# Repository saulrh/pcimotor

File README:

I2C Interface:

--------------------------------------------------
software stop
  0x00

--------------------------------------------------
pause
  0x01

--------------------------------------------------
set controller sensor channel
  0x02

--------------------------------------------------
set controller motor channel
  0x03

--------------------------------------------------
set controller P
  0x04

--------------------------------------------------
set controller I
  0x05

--------------------------------------------------
set controller D
  0x06

--------------------------------------------------
set controller target
  0x07

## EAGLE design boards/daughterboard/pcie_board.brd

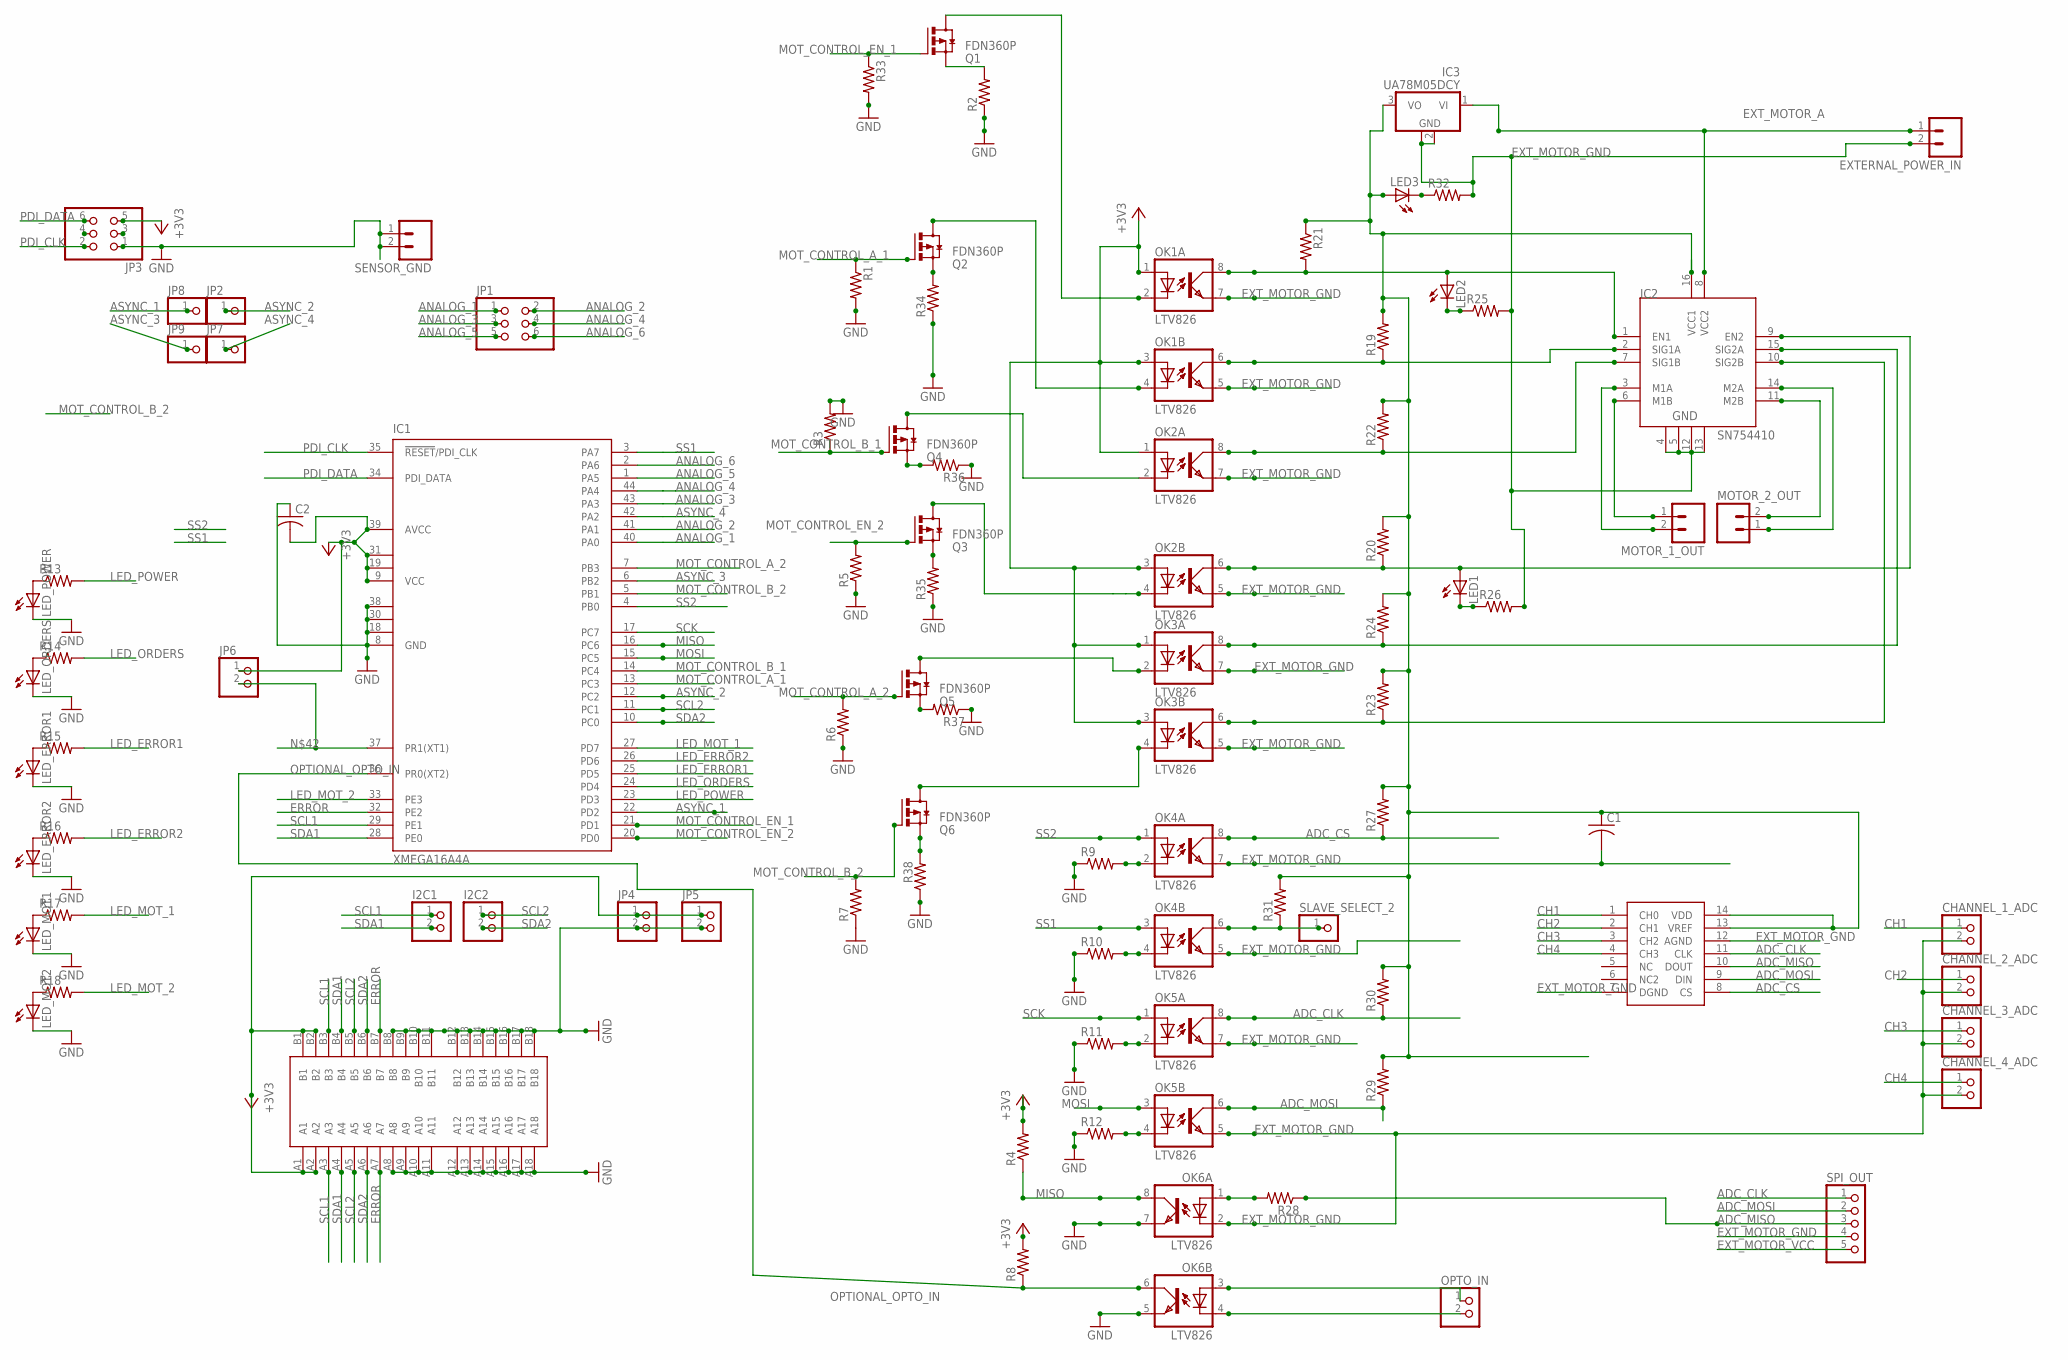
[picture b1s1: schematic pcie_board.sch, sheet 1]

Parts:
C1, C2: C-US025-040X050; C025-040X050
CHANNEL_1_ADC, CHANNEL_2_ADC, CHANNEL_3_ADC, CHANNEL_4_ADC: PINHD-1X2; 1X02
EXTERNAL_POWER_IN: M023.5MM; SCREWTERMINAL-3.5MM-2
I2C1, I2C2: PINHD-1X2; 1X02
IC1: XMEGA16A4A; TQFP44
IC2: SN754410; DIP16
IC3: UA78M05DCY; SOT223
JP1, JP3: PINHD-2X3; 2X03
JP2, JP7, JP8, JP9: PINHD-1X1; 1X01
JP4, JP5, JP6: PINHD-1X2; 1X02
LED1, LED2, LED3: LEDCHIP-LED0603; CHIP-LED0603
LED_ERROR1, LED_ERROR2: LED5MM
LED_MOT1, LED_MOT2: LED5MM
LED_ORDERS: LED5MM
LED_POWER: LED5MM
MOTOR_1_OUT, MOTOR_2_OUT: M023.5MM; SCREWTERMINAL-3.5MM-2
OK1, OK2, OK3, OK4, OK5, OK6: LTV826; DIL08
OPTO_IN: PINHD-1X2; 1X02
Q1, Q2, Q3, Q4, Q5, Q6: FDN360P; SUPER-SOT3
R1, R2, R3, R4, R5, R6, R7, R8, R9, R10, R11, R12, R13, R14, R15, R16, R17, R18, R19, R20, R21, R22, R23, R24, R25, R26, R27, R28, R29, R30, R31, R32, R33, R34, R35, R36, R37, R38: R-US_M0805; M0805
SENSOR_GND: M023.5MM; SCREWTERMINAL-3.5MM-2
SLAVE_SELECT_2: PINHD-1X1; 1X01
SPI_OUT: PINHD-1X5; 1X05
U$1: PCI-E1X_EDGE; PCI-E_X1_EDGE
U$2: MCP3004; DIL14

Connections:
+3V3: C2.2, IC1.9 (VCC), IC1.19 (VCC1), IC1.31 (VCC2), IC1.39 (AVCC), JP3.5, JP4.1, JP5.1, JP6.1, OK1.1 (A), OK1.3 (A), OK2.1 (A), OK2.3 (A), OK3.1 (A), OK3.3 (A), R4.2, R8.2, U$1.A1, U$1.A2, U$1.B1, U$1.B2
ADC_CLK: OK5.8 (COL), R30.1, SPI_OUT.1, U$2.11 (CLK)
ADC_CS: OK4.8 (COL), R27.1, U$2.8 (CS)
ADC_MISO: R28.1, SPI_OUT.3, U$2.10 (DOUT)
ADC_MOSI: OK5.6 (COL), R29.1, SPI_OUT.2, U$2.9 (DIN)
ANALOG_1: IC1.40 (PA0), JP1.1
ANALOG_2: IC1.41 (PA1), JP1.2
ANALOG_3: IC1.43 (PA3), JP1.3
ANALOG_4: IC1.44 (PA4), JP1.4
ANALOG_5: IC1.1 (PA5), JP1.5
ANALOG_6: IC1.2 (PA6), JP1.6
ASYNC_1: IC1.22 (PD2), JP8.1
ASYNC_2: IC1.12 (PC2), JP2.1
ASYNC_3: IC1.6 (PB2), JP9.1
ASYNC_4: IC1.42 (PA2), JP7.1
CH1: CHANNEL_1_ADC.1, U$2.1 (CH0)
CH2: CHANNEL_2_ADC.1, U$2.2 (CH1)
CH3: CHANNEL_3_ADC.1, U$2.3 (CH2)
CH4: CHANNEL_4_ADC.1, U$2.4 (CH3)
ERROR: IC1.32 (PE2), U$1.A7, U$1.B7
EXT_MOTOR_A: EXTERNAL_POWER_IN.1, IC2.8 (VCC2), IC3.1 (VI)
EXT_MOTOR_GND: C1.2, CHANNEL_1_ADC.2, CHANNEL_2_ADC.2, CHANNEL_3_ADC.2, CHANNEL_4_ADC.2, EXTERNAL_POWER_IN.2, IC2.4, IC2.5, IC2.12, IC2.13, IC3.2 (GND), IC3.4 (GND), OK1.5 (EMIT), OK1.7 (EMIT), OK2.5 (EMIT), OK2.7 (EMIT), OK3.5 (EMIT), OK3.7 (EMIT), OK4.5 (EMIT), OK4.7 (EMIT), OK5.5 (EMIT), OK5.7 (EMIT), OK6.2 (C), R25.2, R26.2, R32.2, SPI_OUT.4, U$2.7 (DGND), U$2.12 (AGND)
EXT_MOTOR_VCC: C1.1, IC2.16 (VCC1), IC3.3 (VO), LED3.A, R19.2, R20.2, R21.1, R22.2, R23.2, R24.2, R27.2, R29.2, R30.2, R31.2, SPI_OUT.5, U$2.13 (VREF), U$2.14 (VDD)
GND: C2.1, IC1.8 (GND), IC1.18 (GND1), IC1.30 (GND2), IC1.38 (GND3), JP3.1, JP4.2, JP5.2, LED_ERROR1.K (C), LED_ERROR2.K (C), LED_MOT1.K (C), LED_MOT2.K (C), LED_ORDERS.K (C), LED_POWER.K (C), OK6.5 (EMIT), OK6.7 (EMIT), R1.2, R2.1, R3.2, R5.1, R6.1, R7.1, R9.1, R10.1, R11.1, R12.1, R33.2, R34.1, R35.1, R36.1, R37.1, R38.1, SENSOR_GND.1, SENSOR_GND.2, U$1.A8, U$1.A9, U$1.A10, U$1.A11, U$1.A12, U$1.A13, U$1.A14, U$1.A15, U$1.A16, U$1.A17, U$1.A18, U$1.B8, U$1.B9, U$1.B10, U$1.B11, U$1.B12, U$1.B13, U$1.B14, U$1.B15, U$1.B16, U$1.B17, U$1.B18
LED_ERROR1: IC1.25 (PD5), R15.2
LED_ERROR2: IC1.26 (PD6), R16.2
LED_MOT_1: IC1.27 (PD7), R17.2
LED_MOT_2: IC1.33 (PE3), R18.2
LED_ORDERS: IC1.24 (PD4), R14.2
LED_POWER: IC1.23 (PD3), R13.2
MISO: IC1.16 (PC6), OK6.8 (COL), R4.1
MOSI: IC1.15 (PC5), OK5.3 (A)
MOT_CONTROL_A_1: IC1.13 (PC3), Q2.1 (G), R1.1
MOT_CONTROL_A_2: IC1.7 (PB3), Q5.1 (G), R6.2
MOT_CONTROL_B_1: IC1.14 (PC4), Q4.1 (G), R3.1
MOT_CONTROL_B_2: IC1.5 (PB1), Q6.1 (G), R7.2
MOT_CONTROL_EN_1: IC1.21 (PD1), Q1.1 (G), R33.1
MOT_CONTROL_EN_2: IC1.20 (PD0), Q3.1 (G), R5.2
unnamed: IC2.14 (M2A), MOTOR_2_OUT.1
unnamed: Q1.2 (S), R2.2
unnamed: IC2.11 (M2B), MOTOR_2_OUT.2
unnamed: OK1.2 (C), Q1.3 (D)
unnamed: Q2.2 (S), R34.2
unnamed: OK1.4 (C), Q2.3 (D)
unnamed: Q4.2 (S), R36.2
unnamed: OK4.2 (C), R9.2
unnamed: OK2.4 (C), Q3.3 (D)
unnamed: OK3.2 (C), Q5.3 (D)
unnamed: Q5.2 (S), R37.2
unnamed: OK4.4 (C), R10.2
unnamed: OK5.2 (C), R11.2
unnamed: OK5.4 (C), R12.2
unnamed: Q3.2 (S), R35.2
unnamed: LED_POWER.A, R13.1
unnamed: LED_ORDERS.A, R14.1
unnamed: OK2.2 (C), Q4.3 (D)
unnamed: OK4.6 (COL), R31.1, SLAVE_SELECT_2.1
unnamed: LED_ERROR1.A, R15.1
unnamed: LED_ERROR2.A, R16.1
unnamed: LED_MOT1.A, R17.1
unnamed: LED_MOT2.A, R18.1
unnamed: IC2.1 (EN1), LED2.A, OK1.8 (COL), R21.2
unnamed: IC2.2 (SIG1A), OK1.6 (COL), R19.1
unnamed: LED2.C, R25.1
unnamed: LED1.C, R26.1
unnamed: IC2.9 (EN2), LED1.A, OK2.6 (COL), R20.1
unnamed: IC2.7 (SIG1B), OK2.8 (COL), R22.1
unnamed: IC2.15 (SIG2A), OK3.8 (COL), R24.1
unnamed: IC2.3 (M1A), MOTOR_1_OUT.2
unnamed: IC2.6 (M1B), MOTOR_1_OUT.1
unnamed: IC2.10 (SIG2B), OK3.6 (COL), R23.1
unnamed: OK6.1 (A), R28.2
unnamed: OK6.3 (A), OPTO_IN.1
unnamed: OK6.4 (C), OPTO_IN.2
unnamed: LED3.C, R32.1
unnamed: Q6.2 (S), R38.2
unnamed: OK3.4 (C), Q6.3 (D)
unnamed: IC1.37 (PR1(XT1)), JP6.2
OPTIONAL_OPTO_IN: IC1.36 (PR0(XT2)), OK6.6 (COL), R8.1
PDI_CLK: IC1.35 (!RESET!/PDI_CLK), JP3.2
PDI_DATA: IC1.34 (PDI_DATA), JP3.6
SCK: IC1.17 (PC7), OK5.1 (A)
SCL1: I2C1.1, IC1.29 (PE1), U$1.A3, U$1.B3
SCL2: I2C2.1, IC1.11 (PC1), U$1.A5, U$1.B5
SDA1: I2C1.2, IC1.28 (PE0), U$1.A4, U$1.B4
SDA2: I2C2.2, IC1.10 (PC0), U$1.A6, U$1.B6
SS1: IC1.3 (PA7), OK4.3 (A)
SS2: IC1.4 (PB0), OK4.1 (A)

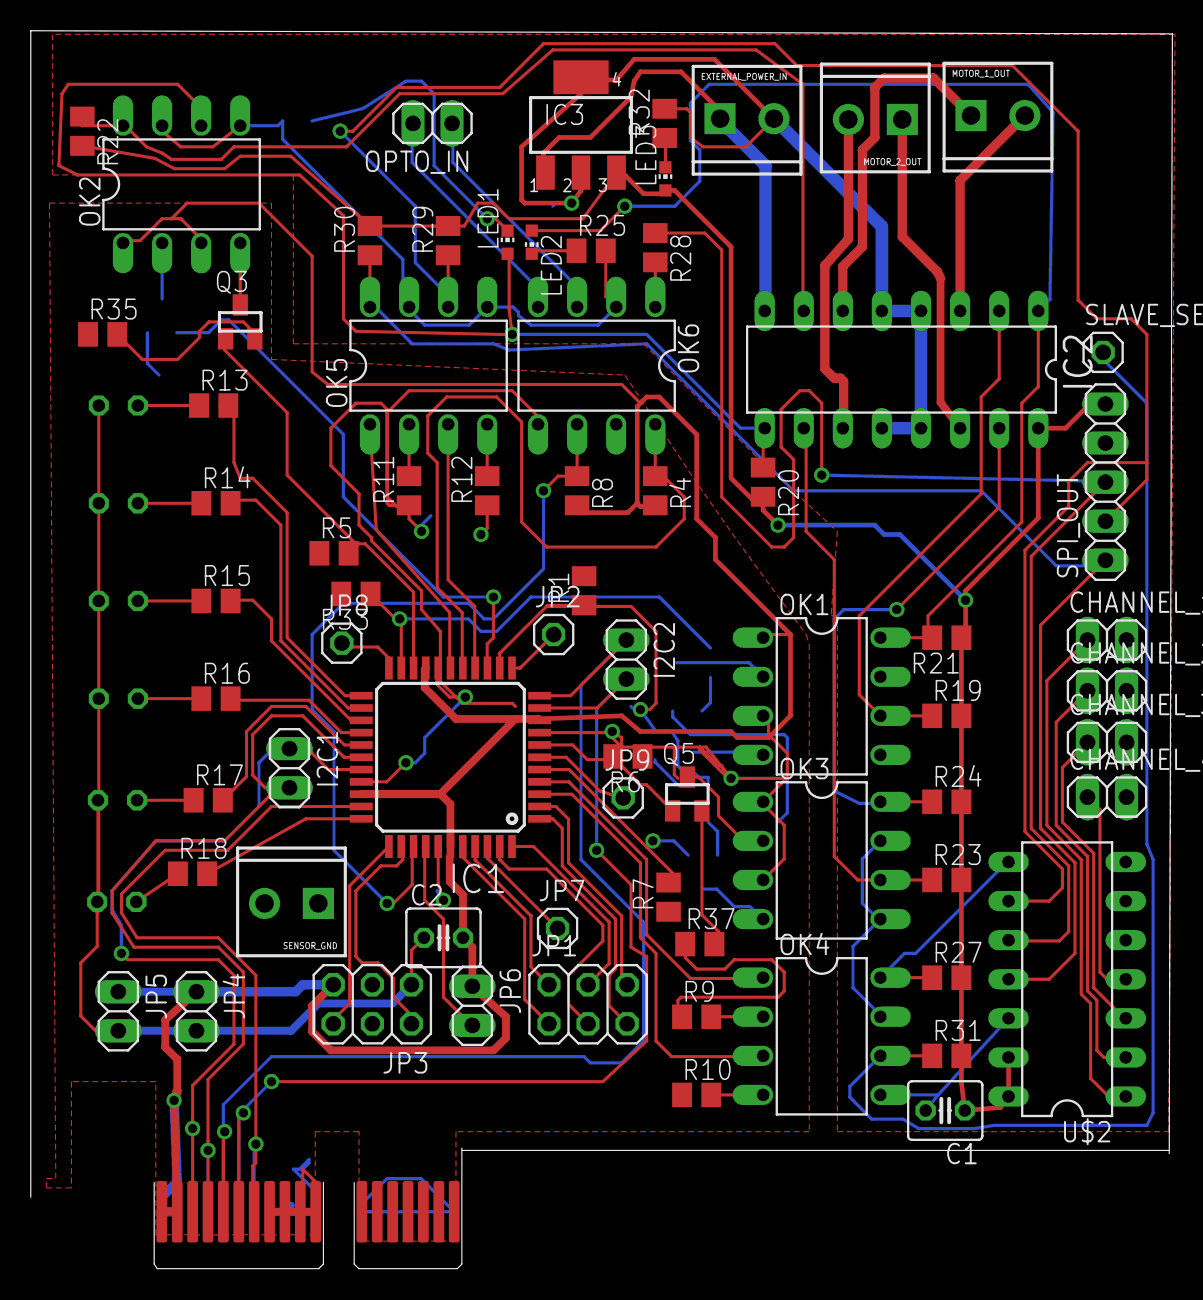
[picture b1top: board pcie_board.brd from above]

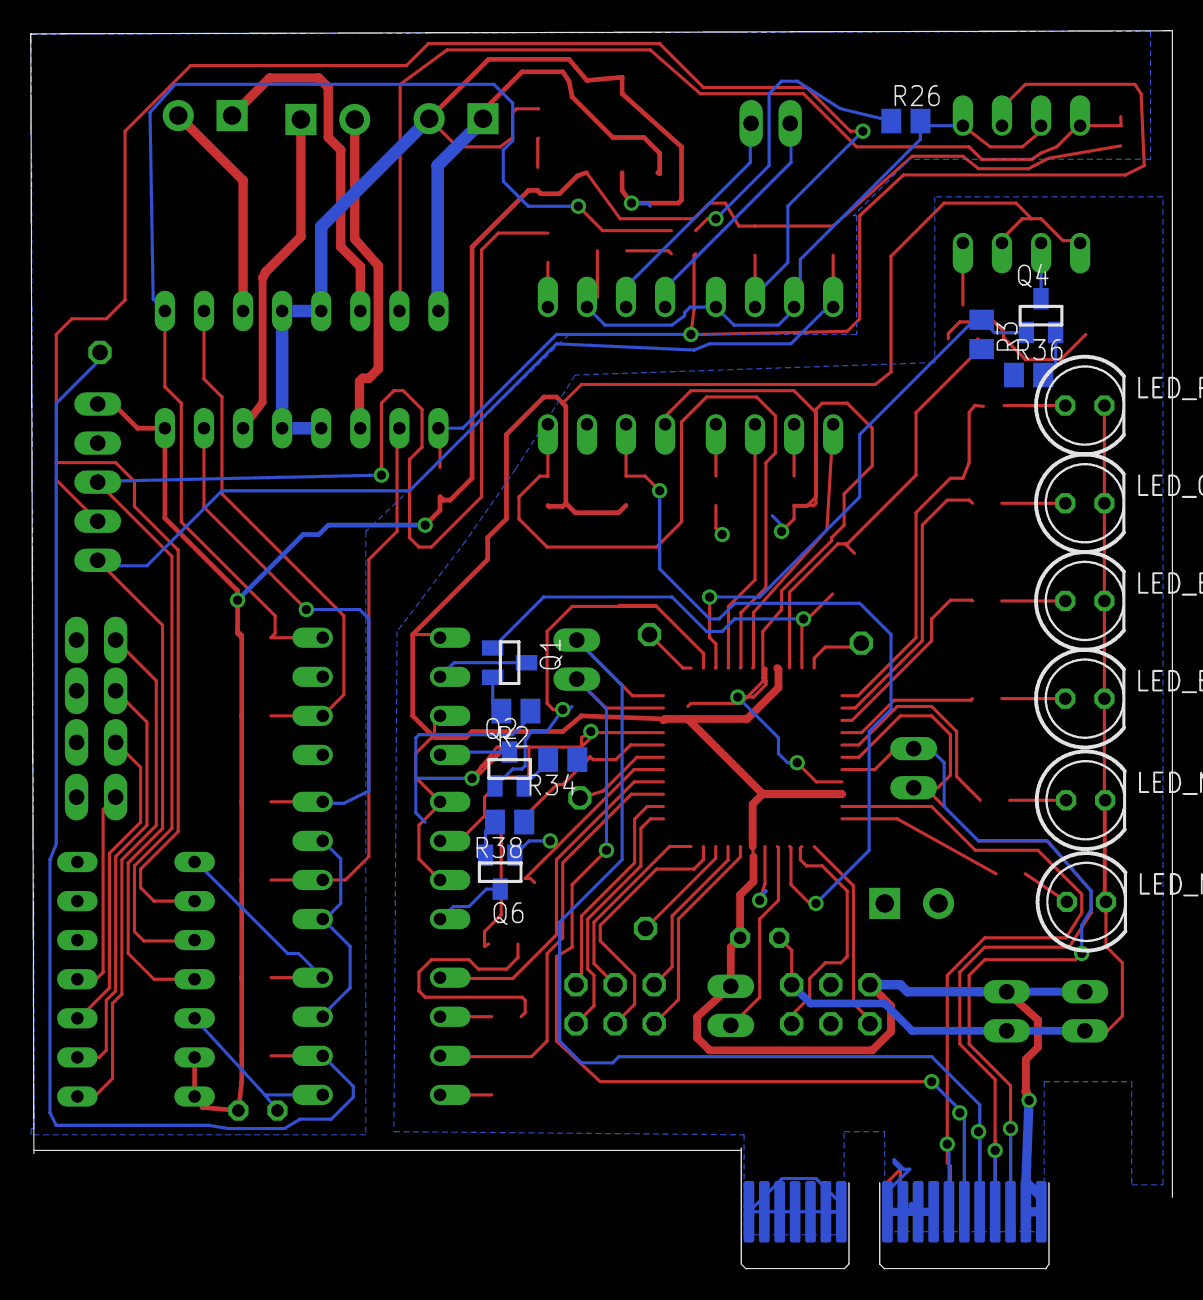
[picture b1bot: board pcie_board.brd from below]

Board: 2 copper layers, 74.1 x 80.4 mm, 88 parts (16 on the bottom side), 88 nets.

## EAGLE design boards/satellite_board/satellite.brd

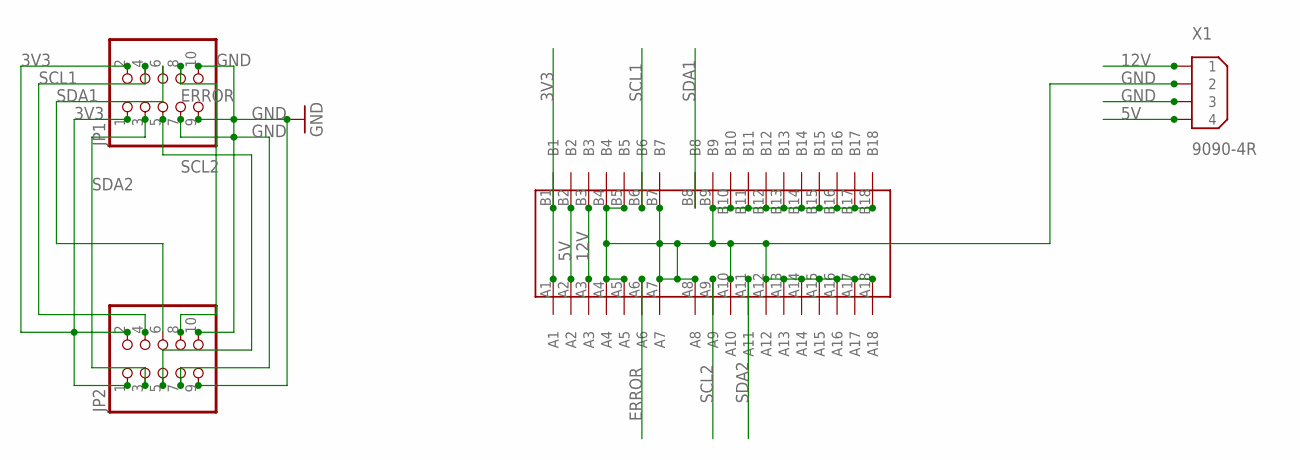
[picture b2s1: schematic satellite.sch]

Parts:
JP1, JP2: PINHD-2X5; 2X05
U$1: PCIE1X
X1: 9090-4R

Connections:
3V3: JP1.1, JP1.2, JP2.1, JP2.2, U$1.A1, U$1.B1
5V: U$1.A2, U$1.B2, X1.4
12V: U$1.A3, U$1.B3, X1.1
ERROR: JP1.8, JP2.8, U$1.A6
GND: JP1.7, JP1.9, JP1.10, JP2.7, JP2.9, JP2.10, U$1.A4, U$1.A5, U$1.A7, U$1.A8, U$1.A10, U$1.A12, U$1.A13, U$1.A14, U$1.A15, U$1.A16, U$1.A17, U$1.A18, U$1.B4, U$1.B5, U$1.B7, U$1.B9, U$1.B10, U$1.B11, U$1.B12, U$1.B13, U$1.B14, U$1.B15, U$1.B16, U$1.B17, U$1.B18, X1.2, X1.3
SCL1: JP1.4, JP2.4, U$1.B6
SCL2: JP1.5, JP2.5, U$1.A9
SDA1: JP1.6, JP2.6, U$1.B8
SDA2: JP1.3, JP2.3, U$1.A11

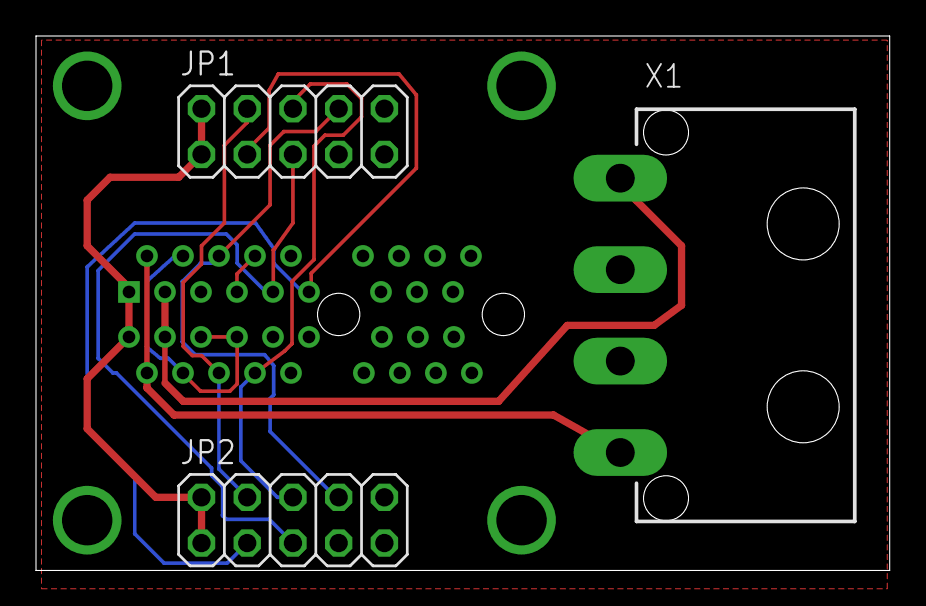
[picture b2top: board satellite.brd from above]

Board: 2 copper layers, 47.4 x 29.7 mm, 4 parts (0 on the bottom side), 9 nets.

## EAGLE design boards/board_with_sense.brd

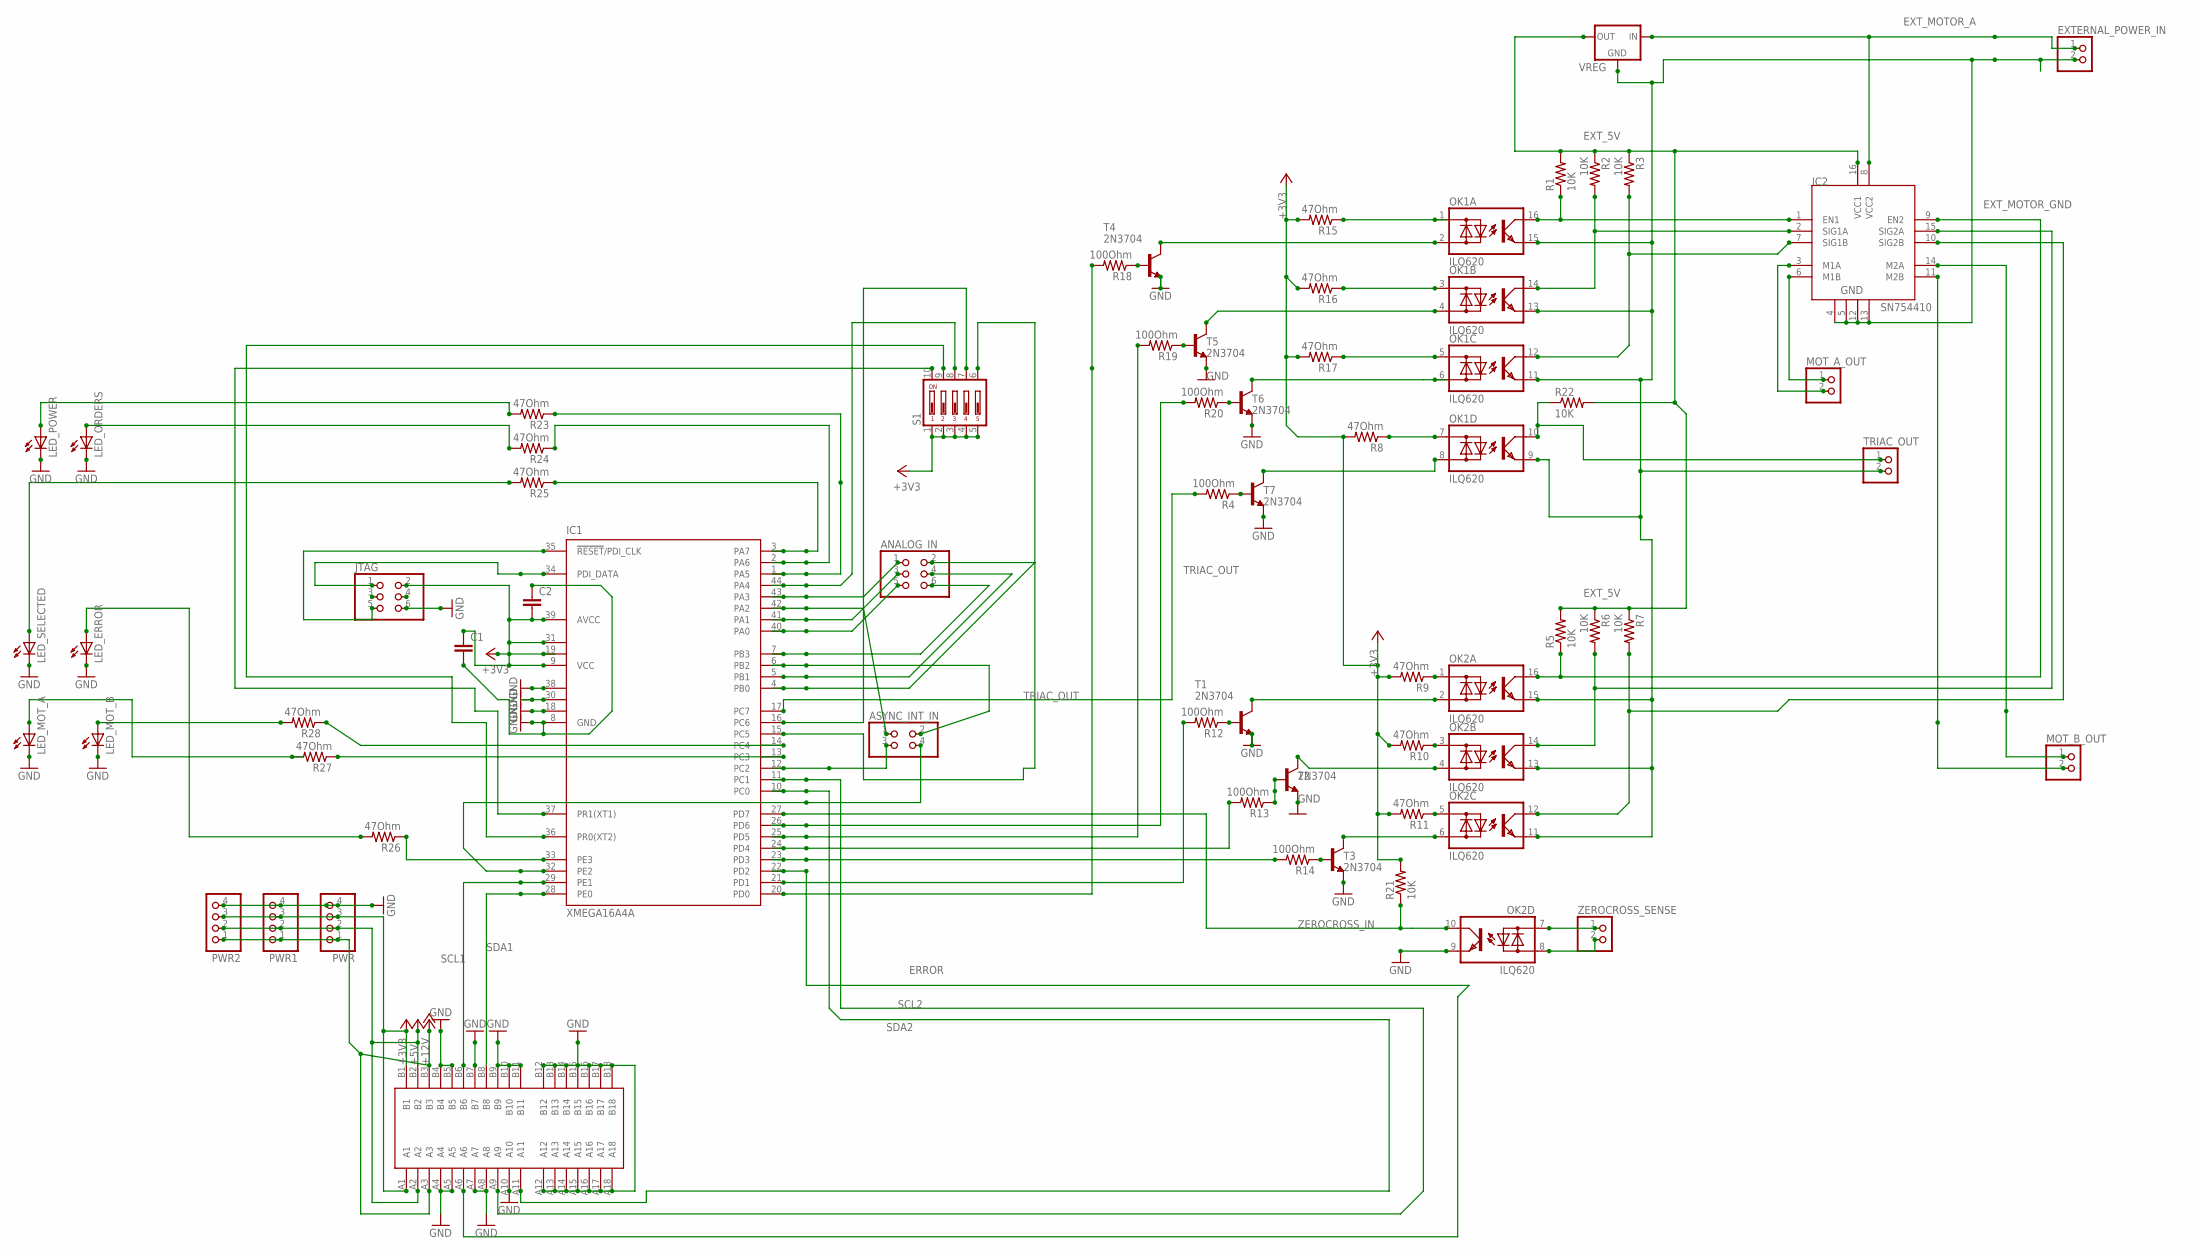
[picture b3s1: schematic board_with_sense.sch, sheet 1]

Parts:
ANALOG_IN: PINHD-2X3; 2X03
ASYNC_INT_IN: PINHD-2X2; 2X02
C1, C2: C2.5/4; C2.5-4
EXTERNAL_POWER_IN: PINHD-1X2; 1X02
IC1: XMEGA16A4A; TQFP44
IC2: SN754410; DIP16
JTAG: PINHD-2X3; 2X03
LED_ERROR: LED5MM
LED_MOT_A: LED5MM
LED_MOT_B: LED5MM
LED_ORDERS: LED5MM
LED_POWER: LED5MM
LED_SELECTED: LED5MM
MOT_A_OUT: PINHD-1X2; 1X02
MOT_B_OUT: PINHD-1X2; 1X02
OK1, OK2: ILQ620; DIL16
PWR, PWR1, PWR2: PINHD-1X4; 1X04
R1, R2, R3, R5, R6, R7, R22: 10K; R0805
R4, R12: 100Ohm; 0207/10
R8, R9, R10, R11, R15, R16, R17: 47Ohm; 0207/10
R13, R14, R18, R19, R20: 100Ohm; R0805
R21: 10K; 0207/10
R23, R24, R25, R26, R27, R28: 47Ohm; 0204/7
S1: DA05; DA-05
T1, T2, T3, T4, T5, T6, T7: 2N3704; TO92
TRIAC_OUT: PINHD-1X2; 1X02
VREG: 78MXXL
X1: PCI-E1X_EDGE; PCI-E_X1_EDGE
ZEROCROSS_SENSE: PINHD-1X2; 1X02

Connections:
+3V3: C1.1, C2.2, IC1.9 (VCC), IC1.19 (VCC1), IC1.31 (VCC2), IC1.39 (AVCC), JTAG.2, PWR.3, PWR1.3, PWR2.3, R8.2, R9.2, R10.2, R11.2, R15.2, R16.2, R17.2, R21.2, S1.1, S1.2, S1.3, S1.4, S1.5, X1.A1, X1.B1
+5V: PWR.2, PWR1.2, PWR2.2, X1.A2, X1.B2
+12V: PWR.1, PWR1.1, PWR2.1, X1.A3, X1.B3
ERROR: IC1.22 (PD2), X1.A6
EXT_5V: IC2.16 (VCC1), R1.2, R2.1, R3.1, R5.2, R6.1, R7.1, R22.2, VREG.OUT
EXT_MOTOR_A: EXTERNAL_POWER_IN.1, IC2.8 (VCC2), VREG.IN
EXT_MOTOR_GND: EXTERNAL_POWER_IN.2, IC2.4, IC2.5, IC2.12, IC2.13, OK1.9 (E), OK1.11 (E), OK1.13 (E), OK1.15 (E), OK2.11 (E), OK2.13 (E), OK2.15 (E), TRIAC_OUT.2, VREG.GND
GND: C1.2, C2.1, IC1.8 (GND), IC1.18 (GND1), IC1.30 (GND2), IC1.38 (GND3), JTAG.6, LED_ERROR.K (C), LED_MOT_A.K (C), LED_MOT_B.K (C), LED_ORDERS.K (C), LED_POWER.K (C), LED_SELECTED.K (C), OK2.9 (E), PWR.4, PWR1.4, PWR2.4, T1.3 (E), T2.3 (E), T3.3 (E), T4.3 (E), T5.3 (E), T6.3 (E), T7.3 (E), X1.A4, X1.A5, X1.A7, X1.A8, X1.A10, X1.A12, X1.A13, X1.A14, X1.A15, X1.A16, X1.A17, X1.A18, X1.B4, X1.B5, X1.B7, X1.B9, X1.B10, X1.B11, X1.B12, X1.B13, X1.B14, X1.B15, X1.B16, X1.B17, X1.B18
unnamed: IC1.3 (PA7), R25.1
unnamed: IC1.35 (!RESET!/PDI_CLK), JTAG.5
unnamed: R4.1, T7.1 (B)
unnamed: LED_POWER.A, R23.2
unnamed: OK1.10 (C), R22.1, TRIAC_OUT.1
unnamed: LED_ORDERS.A, R24.2
unnamed: LED_SELECTED.A, R25.2
unnamed: OK1.7 (AC1), R8.1
unnamed: IC1.34 (PDI_DATA), JTAG.1
unnamed: IC1.33 (PE3), R26.1
unnamed: LED_ERROR.A, R26.2
unnamed: ANALOG_IN.4, IC1.5 (PB1)
unnamed: ANALOG_IN.6, IC1.7 (PB3)
unnamed: ASYNC_INT_IN.3, IC1.12 (PC2)
unnamed: IC1.13 (PC3), R27.1
unnamed: ANALOG_IN.1, IC1.43 (PA3)
unnamed: IC1.14 (PC4), R28.1
unnamed: ASYNC_INT_IN.4, IC1.32 (PE2)
unnamed: LED_MOT_B.A, R28.2
unnamed: IC1.2 (PA6), R24.1
unnamed: ASYNC_INT_IN.2, IC1.6 (PB2)
unnamed: LED_MOT_A.A, R27.2
unnamed: IC1.36 (PR0(XT2)), S1.9
unnamed: IC1.37 (PR1(XT1)), S1.10
unnamed: OK1.8 (AC2), T7.2 (C)
unnamed: OK2.7 (AC1), ZEROCROSS_SENSE.1
unnamed: OK2.2 (AC2), T1.2 (C)
unnamed: OK2.1 (AC1), R9.1
unnamed: IC2.3 (M1A), MOT_A_OUT.2
unnamed: IC2.6 (M1B), MOT_A_OUT.1
unnamed: IC2.1 (EN1), OK1.16 (C), R1.1
unnamed: IC2.2 (SIG1A), OK1.14 (C), R2.2
unnamed: IC2.7 (SIG1B), OK1.12 (C), R3.2
unnamed: OK2.8 (AC2), ZEROCROSS_SENSE.2
unnamed: IC1.20 (PD0), R18.2
unnamed: IC2.11 (M2B), MOT_B_OUT.2
unnamed: IC2.9 (EN2), OK2.16 (C), R5.1
unnamed: IC2.15 (SIG2A), OK2.14 (C), R6.2
unnamed: IC2.10 (SIG2B), OK2.12 (C), R7.2
unnamed: IC2.14 (M2A), MOT_B_OUT.1
unnamed: IC1.16 (PC6), S1.7
unnamed: IC1.15 (PC5), S1.6
unnamed: OK2.3 (AC1), R10.1
unnamed: OK2.5 (AC1), R11.1
unnamed: OK2.4 (AC2), T2.2 (C)
unnamed: OK2.6 (AC2), T3.2 (C)
unnamed: R12.1, T1.1 (B)
unnamed: R13.1, T2.1 (B)
unnamed: R14.1, T3.1 (B)
unnamed: IC1.23 (PD3), R14.2
unnamed: IC1.24 (PD4), R13.2
unnamed: OK1.2 (AC2), T4.2 (C)
unnamed: OK1.4 (AC2), T5.2 (C)
unnamed: OK1.6 (AC2), T6.2 (C)
unnamed: R18.1, T4.1 (B)
unnamed: R19.1, T5.1 (B)
unnamed: R20.1, T6.1 (B)
unnamed: IC1.25 (PD5), R19.2
unnamed: IC1.26 (PD6), R20.2
unnamed: OK1.1 (AC1), R15.1
unnamed: OK1.3 (AC1), R16.1
unnamed: OK1.5 (AC1), R17.1
unnamed: IC1.44 (PA4), S1.8
unnamed: ANALOG_IN.2, IC1.4 (PB0)
unnamed: ANALOG_IN.5, IC1.40 (PA0)
unnamed: ANALOG_IN.3, IC1.41 (PA1)
unnamed: ASYNC_INT_IN.1, IC1.42 (PA2)
unnamed: IC1.1 (PA5), R23.1
PWM_A: IC1.21 (PD1), R12.2
SCL1: IC1.29 (PE1), X1.B6
SCL2: IC1.11 (PC1), X1.A9
SDA1: IC1.28 (PE0), X1.B8
SDA2: IC1.10 (PC0), X1.A11
TRIAC_OUT: IC1.17 (PC7), R4.2
ZEROCROSS_IN: IC1.27 (PD7), OK2.10 (C), R21.1

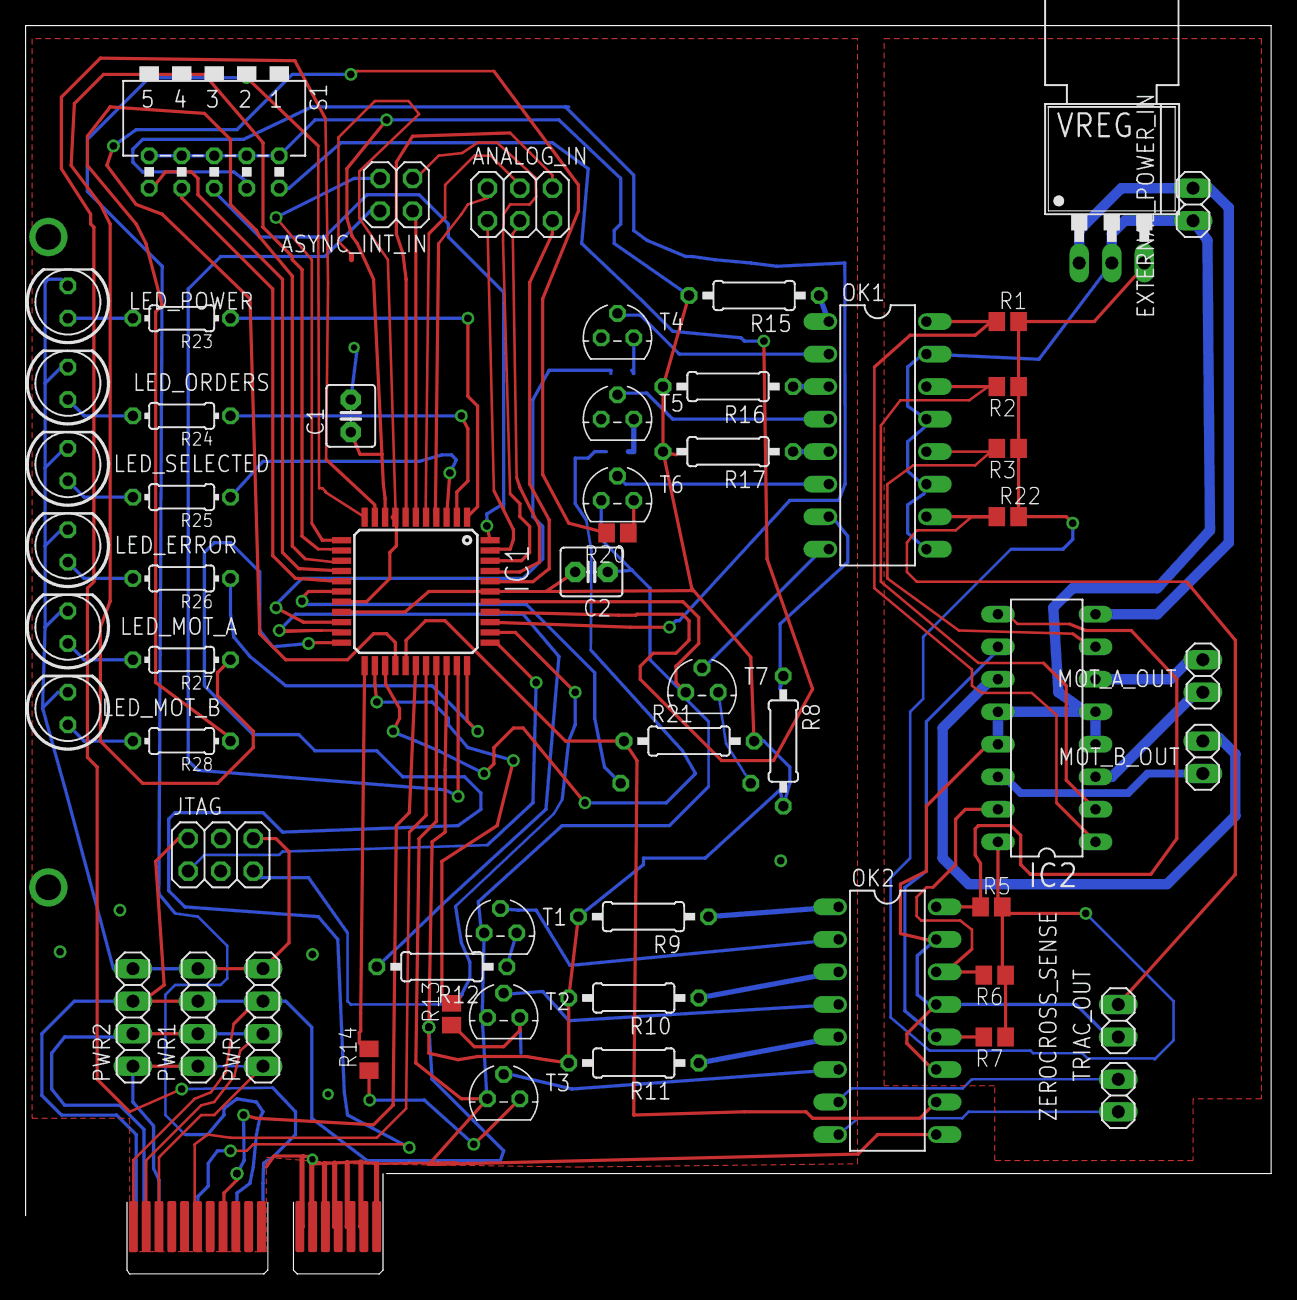
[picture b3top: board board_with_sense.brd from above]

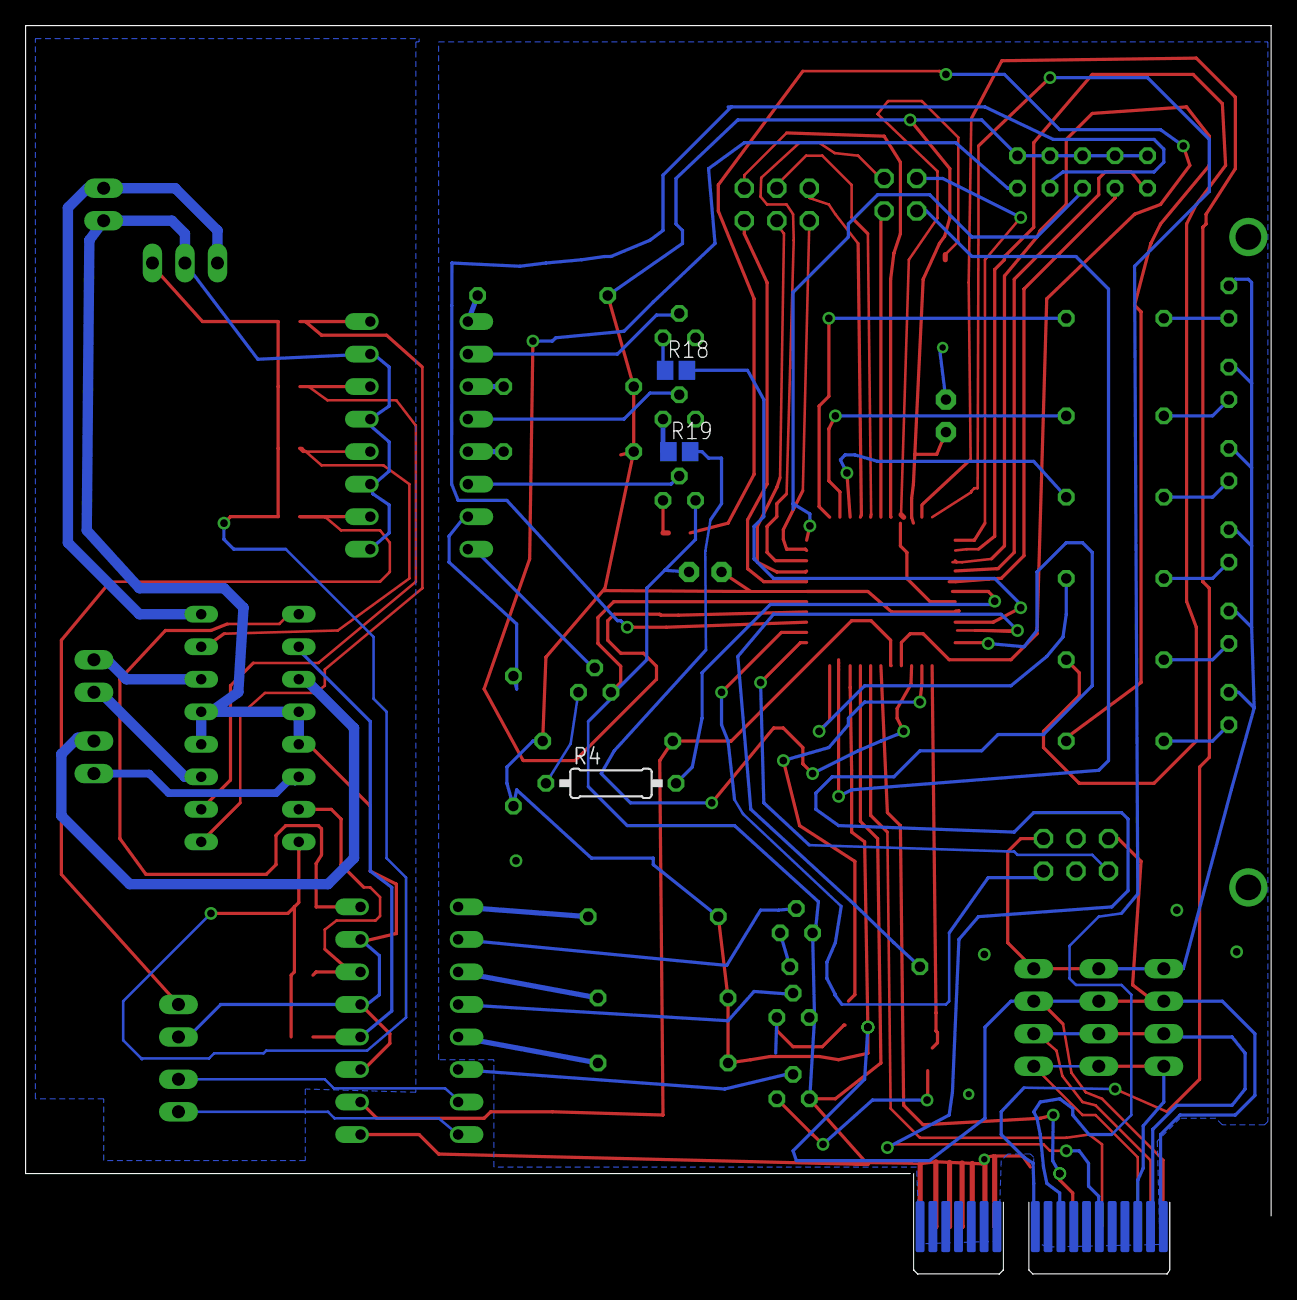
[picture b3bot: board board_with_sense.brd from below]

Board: 2 copper layers, 97.2 x 97.5 mm, 61 parts (3 on the bottom side), 83 nets.

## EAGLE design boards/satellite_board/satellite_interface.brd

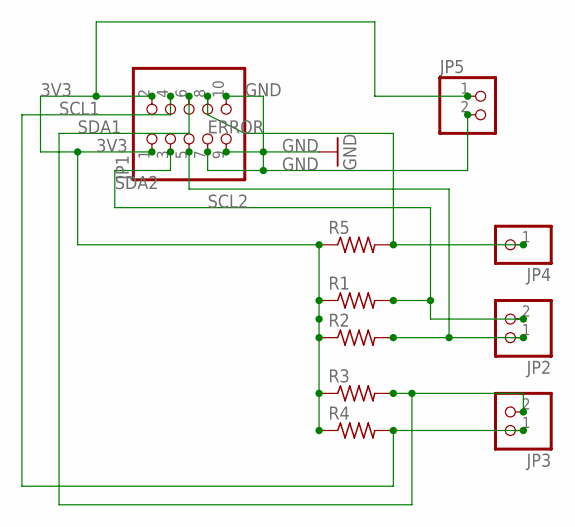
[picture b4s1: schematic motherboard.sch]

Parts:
JP1: PINHD-2X5; 2X05
JP2, JP3, JP5: PINHD-1X2; 1X02
JP4: PINHD-1X1; 1X01
R1, R2, R3, R4, R5: R-US_M0805; M0805

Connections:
3V3: JP1.1, JP1.2, JP5.1, R1.1, R2.1, R3.1, R4.1, R5.1
ERROR: JP1.8, JP4.1, R5.2
GND: JP1.7, JP1.9, JP1.10, JP5.2
SCL1: JP1.4, JP3.1, R4.2
SCL2: JP1.5, JP2.1, R2.2
SDA1: JP1.6, JP3.2, R3.2
SDA2: JP1.3, JP2.2, R1.2

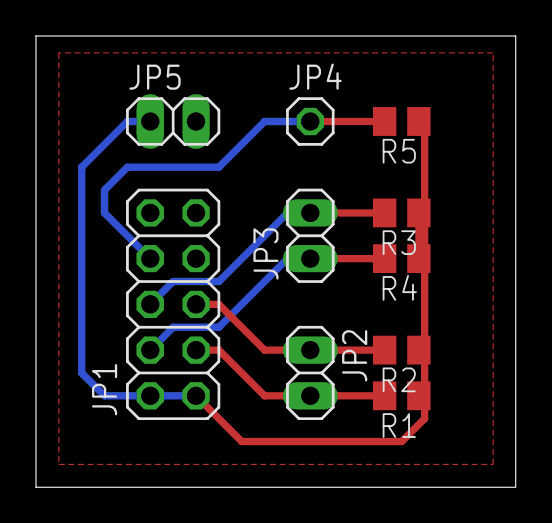
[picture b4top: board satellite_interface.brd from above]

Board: 2 copper layers, 26.7 x 25.1 mm, 10 parts (0 on the bottom side), 7 nets.

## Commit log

2012-04-14 gitignore: Ignore compilation products
2012-04-14 ignore backups
2012-04-14 reformat for reading
2012-04-14 new makefile from better source
2012-04-14 add file for daughterboard
2012-04-14 ignore a bunch of stuff from compilation
2012-04-14 default is to compile without programming
2012-04-16 Add clksys_driver and docs for same
2012-04-16 LCD IO test: Should turn on all the LCDs.
2012-04-16 Accidentally left a hanging define. fixed.
2012-04-16 makefile: include clksys_driver code.
2012-04-16 daughterboard: write code for setting up clocks
2012-04-16 daughterboard: run code for setting up clocks.
2012-04-18 Using avrispmkii instead of jtagice
2012-04-20 Add TWI library
2012-04-20 Add TWI library to makefile
2012-04-20 Add large comments to indicate organization
2012-04-20 make the LEDs flash faster
2012-04-20 Add TWI - hopefully
2012-04-20 Add daughterboard.h for function prototypes
2012-04-20 Add defines so we can refer to peripherals symbolically
2012-04-21 fixed bug in pin definitions
2012-04-21 add declarations chunk
2012-04-21 use symbolic pin name declarations and multipin config
2012-04-21 change comment
2012-04-21 only enable the pins we're using
2012-04-21 take out debug comment
2012-04-21 display received twi data on leds
2012-04-21 change to I2C interface 2
2012-04-21 reorganize file
2012-04-21 Rename functions and reorganize header
2012-04-21 Make clock run faster
2012-04-21 start up summary of i2c command protocol
2012-04-23 Moved everything around a lot.
2012-04-23 Fix makefile to accompany movements.
2012-04-23 Fixed includes in daughterboard.c for movements.
2012-04-23 New code for handling LEDs
2012-04-23 New typedefs for things
2012-04-23 Rough draft of I2C interface
2012-04-23 daughterboard.h: Fixed typedefs for sensor_t
2012-04-23 The readme turned into an interface spec. Renamed.
2012-04-23 update readme for more information
2012-04-23 Reorganize so we can add drivers and boards later
2012-04-23 Remove clksys documentation.
2012-04-23 added the board design files
2012-04-23 reorganized the boards into folders
2012-04-23 Removed duplicate files. Use tags for marking revs
2012-04-24 moved stuff around to allow for more boards
2012-04-24 added the eagle libraries, as well as the satellite board
2012-04-24 added the interface board to talk to the ribbon cable of the satellite board
2012-04-24 Rename boards to standardized names
2012-04-24 Add licenses - gpl v2
2012-04-25 remove old "license"
2012-04-27 daughterboard: Define structs for motors and controller
2012-04-27 daughterboard: start changing over to hardware pwm
2012-04-28 fixed the timer from port C to port D
2012-04-28 Added the code in do_motor for setting the direction and the duty cycle
2012-04-28 fixing random bugs - working toward motor pwm
2012-04-28 almost got tcd0 set up.
2012-04-28 Add driver for watchdog timer
2012-04-28 Link in code for watchdog timer
2012-04-28 avr_compiler: Remove definitions for compilers other than avr-gcc
2012-04-28 daughterboard.h: Fix definitions for digital pins
2012-04-28 daughterboard.c: include watchdog timer
2012-04-28 daughterboard.c: set and handle watchdog timer
2012-04-28 Start changing LEDs over to malloc's structs
2012-04-28 Add crude parallel output on digital pins
2012-04-28 Finish converting leds to malloc'd structs
2012-04-28 Set up clock for PWMing the motor ouputs
2012-04-29 bigger digital write buffer
2012-04-29 slower!
2012-04-29 digital write now pushes a fully byte using hte analog pins
2012-04-29 cycle-saving tweak to digout
2012-04-29 Take off debug outputs from clock ISRs
2012-04-29 Functional i2c - displays received data on digout
2012-04-29 Tweak i2c initialization
2012-04-29 remove commented-out response
2012-04-29 Fix up motor duty cycle - simple version
2012-04-29 Flash LEDs when motor is on
2012-04-29 Fix duty cycle
2012-04-29 Use motor b instead of motor A so we have an LED.
2012-04-29 Added an i2c header file defining the commands
2012-04-30 added the switch statement, as well as the get all data function
2012-05-02 i2c commands: turns out that avr has 32-bit floats
2012-05-02 daughterboard: can control two motors!
2012-05-03 Latest board(the one presented at class
2012-05-04 added some fets to take care of the overloaded atxmega.

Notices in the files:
parts and their libraries:
SparkFun: Licensing: CC v3.0 Share-Alike You are welcome to use this library for commercial purposes.
